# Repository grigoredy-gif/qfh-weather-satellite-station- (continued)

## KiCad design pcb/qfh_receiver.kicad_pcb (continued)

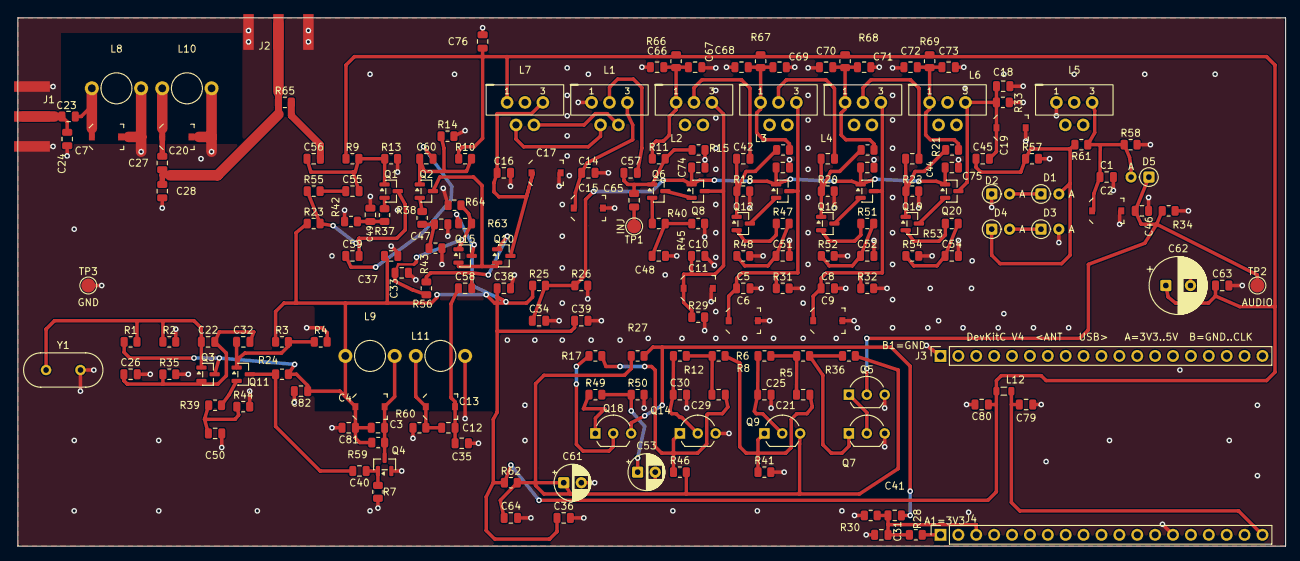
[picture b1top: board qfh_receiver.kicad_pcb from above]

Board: 2 copper layers, 180.0 x 75.0 mm, 196 parts (0 on the bottom side), 84 nets.

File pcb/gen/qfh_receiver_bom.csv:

"Refs","Value","Spec","Footprint","MPN","Farnell","Qty","DNP"
"C1,C5,C8,C10,C14,C16,C18,C24,C28","56p","NP0/C0G ceramic 0805, 50 V","Capacitor_SMD:C_0805_2012Metric","","","9",""
"C2,C6,C9,C11,C15,C17,C19","6.5-30p","Murata TZC3 film trimmer, top adjust","Capacitor_SMD:C_Trimmer_Murata_TZC3","TZC3P300A110R00","2456139","7",""
"C3","3.3p","NP0/C0G ceramic 0805, 50 V","Capacitor_SMD:C_0805_2012Metric","","","1",""
"C4,C7,C13,C20","3-10p","Murata TZC3 film trimmer, top adjust","Capacitor_SMD:C_Trimmer_Murata_TZC3","TZC3R100A110R00","2456140RL","4",""
"C12","5.6p","NP0/C0G ceramic 0805, 50 V","Capacitor_SMD:C_0805_2012Metric","","","1",""
"C21","2.7n","X7R ceramic 0805, 50 V","Capacitor_SMD:C_0805_2012Metric","","","1",""
"C22","82p","NP0/C0G ceramic 0805, 50 V","Capacitor_SMD:C_0805_2012Metric","","","1",""
"C23,C27","8.2p","NP0/C0G ceramic 0805, 50 V","Capacitor_SMD:C_0805_2012Metric","","","2",""
"C25,C31","2.2n","X7R ceramic 0805, 50 V","Capacitor_SMD:C_0805_2012Metric","","","2",""
"C26","180p","NP0/C0G ceramic 0805, 50 V","Capacitor_SMD:C_0805_2012Metric","","","1",""
"C29","8.2n","X7R ceramic 0805, 50 V","Capacitor_SMD:C_0805_2012Metric","","","1",""
"C30","1.2n","X7R ceramic 0805, 50 V","Capacitor_SMD:C_0805_2012Metric","","","1",""
"C32,C33,C47","10n","X7R ceramic 0805, 50 V","Capacitor_SMD:C_0805_2012Metric","","","3",""
"C34,C36-C39,C48-C52,C54,C63,C64,C66-C82","100n","X7R ceramic 0805, 50 V","Capacitor_SMD:C_0805_2012Metric","","","30",""
"C35,C46","47p","NP0/C0G ceramic 0805, 50 V","Capacitor_SMD:C_0805_2012Metric","","","2",""
"C40,C42-C45,C55-C60,C65","1n","X7R ceramic 0805, 50 V","Capacitor_SMD:C_0805_2012Metric","","","12",""
"C41","1u","X7R ceramic 0805, 16 V or more","Capacitor_SMD:C_0805_2012Metric","","","1",""
"C53,C61","100u","electrolytic 10 V, radial D5 P2.5","Capacitor_THT:CP_Radial_D5.0mm_P2.50mm","","","2",""
"C62","1000u","electrolytic 10 V low ESR, radial D8 P3.5","Capacitor_THT:CP_Radial_D8.0mm_P3.50mm","","","1",""
"D1-D4","1N4148","DO-35","Diode_THT:D_DO-35_SOD27_P2.54mm_Vertical_AnodeUp","","","4",""
"D5","1N5711","Schottky, DO-35","Diode_THT:D_DO-35_SOD27_P2.54mm_Vertical_AnodeUp","","","1",""
"J1","SMA antenna","Amphenol edge-launch SMA","Connector_Coaxial:SMA_Amphenol_132289_EdgeMount","132289","2112467","1",""
"J2","SMA test (DNP)","Amphenol edge-launch SMA","Connector_Coaxial:SMA_Amphenol_132289_EdgeMount","132289","2112467","1","DNP"
"J3","ESP32 row B","female header 1x19, 2.54 mm, 8.5 mm stand-off (socket for ESP32-DevKitC V4 38-pin)","Connector_PinSocket_2.54mm:PinSocket_1x19_P2.54mm_Vertical","","","1",""
"J4","ESP32 row A","female header 1x19, 2.54 mm, 8.5 mm stand-off (socket for ESP32-DevKitC V4 38-pin)","Connector_PinSocket_2.54mm:PinSocket_1x19_P2.54mm_Vertical","","","1",""
"L1","2.2u tap13/27","T37-6 toroid: 27 t 0.4 mm enamelled, tap at turn 13, plus 3 t link winding on pads 4/5; mount on edge","qfh_receiver:TOROID_T37-6_UNIVERSAL","","","1",""
"L2-L4","2.2u tap13/27","T37-6 toroid: 27 t 0.4 mm enamelled, tap at turn 13; mount on edge","qfh_receiver:TOROID_T37-6_UNIVERSAL","","","3",""
"L5,L6","2.2u","T37-6 toroid: 27 t 0.4 mm enamelled; mount on edge","qfh_receiver:TOROID_T37-6_UNIVERSAL","","","2",""
"L7","2.2u","T37-6 toroid: 27 t 0.4 mm enamelled, plus 3 t link winding on pads 4/5; mount on edge","qfh_receiver:TOROID_T37-6_UNIVERSAL","","","1",""
"L8,L10","82n","air coil: 5 t 0.8 mm enamelled on a 5 mm former, one diameter from its pair","qfh_receiver:AIRCOIL_5MM","","","2",""
"L9,L11","150n","air coil: 7 t 0.8 mm enamelled on a 5 mm former, one diameter from its pair","qfh_receiver:AIRCOIL_5MM","","","2",""
"L12","FB 600R@100MHz","ferrite bead 0805, 600 ohm at 100 MHz, >= 200 mA","Inductor_SMD:L_0805_2012Metric","","","1",""
"Q1-Q4,Q6,Q8,Q10-Q13,Q15-Q17,Q19,Q20","BFR92P","Infineon SOT-23 (min 5, multiples of 5 at Farnell)","Package_TO_SOT_SMD:SOT-23","BFR92PE6327HTSA1","","15",""
"Q5,Q7,Q14","2N3906","TO-92, E-B-C pinout","Package_TO_SOT_THT:TO-92_Inline_Wide","","","3",""
"Q9,Q18","2N3904","TO-92, E-B-C pinout","Package_TO_SOT_THT:TO-92_Inline_Wide","","","2",""
"R1","9.1k","thick film 0805, 1 %","Resistor_SMD:R_0805_2012Metric","","","1",""
"R2,R5,R7,R8,R26,R28,R29,R31-R33,R36,R46,R56","10k","thick film 0805, 1 %","Resistor_SMD:R_0805_2012Metric","","","13",""
"R3,R14,R15,R18,R20,R22","11k","thick film 0805, 1 %","Resistor_SMD:R_0805_2012Metric","","","6",""
"R4","5.1k","thick film 0805, 1 %","Resistor_SMD:R_0805_2012Metric","","","1",""
"R6,R12","7.5k","thick film 0805, 1 %","Resistor_SMD:R_0805_2012Metric","","","2",""
"R9,R50","820","thick film 0805, 1 %","Resistor_SMD:R_0805_2012Metric","","","2",""
"R10,R11,R16,R19,R21","27k","thick film 0805, 1 %","Resistor_SMD:R_0805_2012Metric","","","5",""
"R13,R35","560","thick film 0805, 1 %","Resistor_SMD:R_0805_2012Metric","","","2",""
"R17","1k","thick film 0805, 1 %","Resistor_SMD:R_0805_2012Metric","","","1",""
"R23","120","thick film 0805, 1 %","Resistor_SMD:R_0805_2012Metric","","","1",""
"R24,R45,R48,R52,R54","330","thick film 0805, 1 %","Resistor_SMD:R_0805_2012Metric","","","5",""
"R25,R60","6.8k","thick film 0805, 1 %","Resistor_SMD:R_0805_2012Metric","","","2",""
"R27","3.3k","thick film 0805, 1 %","Resistor_SMD:R_0805_2012Metric","","","1",""
"R30","6.2k","thick film 0805, 1 %","Resistor_SMD:R_0805_2012Metric","","","1",""
"R34","220k","thick film 0805, 1 %","Resistor_SMD:R_0805_2012Metric","","","1",""
"R37","2.2","thick film 0805, 1 %","Resistor_SMD:R_0805_2012Metric","","","1",""
"R38,R62","100","thick film 0805, 1 %","Resistor_SMD:R_0805_2012Metric","","","2",""
"R39,R42","47","thick film 0805, 1 %","Resistor_SMD:R_0805_2012Metric","","","2",""
"R40,R47,R51,R53","180","thick film 0805, 1 %","Resistor_SMD:R_0805_2012Metric","","","4",""
"R41","4.7k","thick film 0805, 1 %","Resistor_SMD:R_0805_2012Metric","","","1",""
"R43","220","thick film 0805, 1 %","Resistor_SMD:R_0805_2012Metric","","","1",""
"R44","68","thick film 0805, 1 %","Resistor_SMD:R_0805_2012Metric","","","1",""
"R49","270","thick film 0805, 1 %","Resistor_SMD:R_0805_2012Metric","","","1",""
"R55","470","thick film 0805, 1 %","Resistor_SMD:R_0805_2012Metric","","","1",""
"R57","100k","thick film 0805, 1 %","Resistor_SMD:R_0805_2012Metric","","","1",""
"R58","47k","thick film 0805, 1 %","Resistor_SMD:R_0805_2012Metric","","","1",""
"R59","2.2k","thick film 0805, 1 %","Resistor_SMD:R_0805_2012Metric","","","1",""
"R61","33k","thick film 0805, 1 %","Resistor_SMD:R_0805_2012Metric","","","1",""
"R63","13k","thick film 0805, 1 %","Resistor_SMD:R_0805_2012Metric","","","1",""
"R64","15k","thick film 0805, 1 %","Resistor_SMD:R_0805_2012Metric","","","1",""
"R65","0R link","thick film 0805, 1 %","Resistor_SMD:R_0805_2012Metric","","","1",""
"R66-R69","10R","thick film 0805, 1 %","Resistor_SMD:R_0805_2012Metric","","","4",""
"TP1","inject 12.9M","","TestPoint:TestPoint_Pad_D2.0mm","","","1",""
"TP2","audio mon","","TestPoint:TestPoint_Pad_D2.0mm","","","1",""
"TP3","gnd","","TestPoint:TestPoint_Pad_D2.0mm","","","1",""
"Y1","25.000MHz","HC-49/S, FUNDAMENTAL mode (not overtone), CL 18-20 pF","Crystal:Crystal_HC49-4H_Vertical","","","1",""
